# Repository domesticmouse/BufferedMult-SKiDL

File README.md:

# Eurorack Buffered Multiple (SKiDL + KiCad 10)

A precision **Triple 1-to-3 (Normalized to 1-to-6 / 1-to-9) Eurorack Buffered Multiple** designed in Python using [SKiDL](https://devbisme.github.io/skidl/) and targeting **KiCad 10**.

This project is a SKiDL re-implementation and 3-channel expansion of [domesticmouse/Buffered-Mult](https://github.com/domesticmouse/Buffered-Mult), omitting the LED feedback circuitry.

**Interactive Course & Tutorial:** [**https://domesticmouse.github.io/BufferedMult-SKiDL/**](https://domesticmouse.github.io/BufferedMult-SKiDL/) *(published via GitHub Pages from [`tutorial/`](tutorial/))*

---

## Features & Architecture

- **Triple 1-to-3 / Cascaded 1-to-6 / 1-to-9 Routing**:
  - **Channel 1**: 1 input (`IN_1`) driving 3 individually buffered outputs (`OUT_1A`, `OUT_1B`, `OUT_1C`). When `IN_1` is unpatched, its normalled switch contact (`TN`) grounds the input to `0V`.
  - **Channel 2**: 1 input (`IN_2`) driving 3 individually buffered outputs (`OUT_2A`, `OUT_2B`, `OUT_2C`). When `IN_2` is unpatched, its normalled switch contact (`TN`) receives the buffered signal from Channel 1 (`CH1_BUF`), cascading Channels 1 and 2 into a **1-to-6 buffered multiple** with zero loading droop between channels. Patching a cable into `IN_2` breaks the normal connection for independent channel operation.
  - **Channel 3**: 1 input (`IN_3`) driving 3 individually buffered outputs (`OUT_3A`, `OUT_3B`, `OUT_3C`). When `IN_3` is unpatched, its normalled switch contact (`TN`) receives the buffered signal from Channel 2 (`CH2_BUF`), cascading all three channels into a **1-to-9 buffered multiple** (or a **1-to-3 + 1-to-6** split if `IN_2` is patched while `IN_3` is unpatched). Patching a cable into `IN_3` breaks the normal connection for independent triple 1-to-3 operation.
- **Dedicated Input & Output Buffering**:
  - Each channel uses one quad `TL074H` (`TL074HIDR`) op-amp (`SOIC-14`):
    - **Stage A**: Unity-gain input follower protected by a `PESD12VL1BA` (`SOD-323`) bidirectional 12V TVS/ESD diode, a `100K` input pull-down resistor (`0603`), and a `1K` series input current-limiting resistor (`0603`).
    - **Stages B, C, D**: Three independent unity-gain output followers, each isolated with a `470R` series output protection resistor (`0603`).
- **Eurorack Power Supply Protection**:
  - Standard 10-pin (`2x5`) through-hole shrouded IDC power header (`±12V`, `GND`).
  - Reverse-polarity protection via `1N5819WS` Schottky diodes (`SOD-323`, or `B5819W` in `SOD-123` as a larger alternative).
  - `10uF` radial through-hole electrolytic bulk bypass capacitors per rail plus `100nF` (`0603`) local ceramic decoupling capacitors at each op-amp's `V+` and `V-` pins.

### Signal Flow

```mermaid
flowchart LR
    subgraph CH1["Channel 1 (U1: TL074H)"]
        J_IN1["IN_1 Jack<br/>(TN -> GND)"] --> TVS1["PESD12VL1BA TVS<br/>+ 100K to GND"]
        TVS1 --> R_IN1["1K Series"] --> U1A["U1A Input Buffer"]
        U1A --> U1B["U1B Buffer + 470R"] --> OUT_1A["OUT_1A Jack"]
        U1A --> U1C["U1C Buffer + 470R"] --> OUT_1B["OUT_1B Jack"]
        U1A --> U1D["U1D Buffer + 470R"] --> OUT_1C["OUT_1C Jack"]
    end

    subgraph CH2["Channel 2 (U2: TL074H)"]
        J_IN2["IN_2 Jack<br/>(TN <- CH1_BUF)"] --> TVS2["PESD12VL1BA TVS<br/>+ 100K to GND"]
        TVS2 --> R_IN2["1K Series"] --> U2A["U2A Input Buffer"]
        U2A --> U2B["U2B Buffer + 470R"] --> OUT_2A["OUT_2A Jack"]
        U2A --> U2C["U2C Buffer + 470R"] --> OUT_2B["OUT_2B Jack"]
        U2A --> U2D["U2D Buffer + 470R"] --> OUT_2C["OUT_2C Jack"]
    end

    subgraph CH3["Channel 3 (U3: TL074H)"]
        J_IN3["IN_3 Jack<br/>(TN <- CH2_BUF)"] --> TVS3["PESD12VL1BA TVS<br/>+ 100K to GND"]
        TVS3 --> R_IN3["1K Series"] --> U3A["U3A Input Buffer"]
        U3A --> U3B["U3B Buffer + 470R"] --> OUT_3A["OUT_3A Jack"]
        U3A --> U3C["U3C Buffer + 470R"] --> OUT_3B["OUT_3B Jack"]
        U3A --> U3D["U3D Buffer + 470R"] --> OUT_3C["OUT_3C Jack"]
    end

    U1A -- "CH1_BUF (Normalled to IN_2 TN)" --> J_IN2
    U2A -- "CH2_BUF (Normalled to IN_3 TN)" --> J_IN3
```

---

## Bill of Materials (BOM)

The design separates **SMT components** (factory-assembled on `B.Cu` by JLCPCB) from **Through-Hole (THT) components** (hand-soldered after receiving the boards):

| Ref | Qty | Value / Part | Package / Footprint | KiCad Symbol | LCSC Part # | Assembly / Description |
| :--- | --: | :--- | :--- | :--- | :--- | :--- |
| `U1`–`U3` | 3 | `TL074H` (`TL074HIDR`) | `Package_SO:SOIC-14_3.9x8.7mm_P1.27mm` | `Amplifier_Operational:TL074` | `C2878713` | **SMT (`B.Cu`, Extended)** — Quad Low-Noise High-Voltage Op-Amp |
| `D1`, `D2` | 2 | `1N5819WS` | `Diode_SMD:D_SOD-323` | `Device:D_Schottky` | `C191023` | **SMT (`B.Cu`, Basic)** — Schottky Reverse-Polarity Protection Diode *(Alt larger package: `B5819W` in `Diode_SMD:D_SOD-123`, LCSC `C8598`, Basic)* |
| `D3`–`D5` | 3 | `PESD12VL1BA` (`PESD12VL1BA,115`) | `Diode_SMD:D_SOD-323` | `Device:D_TVS` | `C38558` | **SMT (`B.Cu`, Extended)** — 12V Bidirectional Low-Capacitance (`19 pF`, `<50 nA`) Input ESD/TVS Protection Diode *(Alt 15V: `PESD15VL1BA,115` / `C85378`; Basic SOD-123FL: `SMF12CA` / `C19077508`)* |
| `C3`–`C8` | 6 | `100nF` (`50V X7R`) | `Capacitor_SMD:C_0603_1608Metric` | `Device:C` | `C14663` | **SMT (`B.Cu`, Basic)** — Ceramic Decoupling Capacitor (`CC0603KRX7R9BB104`) |
| `R1`, `R6`, `R11` | 3 | `100K` (`1%`) | `Resistor_SMD:R_0603_1608Metric` | `Device:R` | `C25803` | **SMT (`B.Cu`, Basic)** — Input Pull-Down Resistor (`0603WAF1003T5E`) |
| `R2`, `R7`, `R12` | 3 | `1K` (`1%`) | `Resistor_SMD:R_0603_1608Metric` | `Device:R` | `C21190` | **SMT (`B.Cu`, Basic)** — Input Series Overvoltage / ESD Current-Limiting Resistor (`0603WAF1001T5E`) |
| `R3`–`R5`, `R8`–`R10`, `R13`–`R15` | 9 | `470R` (`1%`) | `Resistor_SMD:R_0603_1608Metric` | `Device:R` | `C23179` | **SMT (`B.Cu`, Basic)** — Output Series Protection Resistor (`0603WAF4700T5E`) |
| `J2`–`J13` | 12 | `WQP-PJ398SM` | `Connector_Audio:Jack_3.5mm_QingPu_WQP-PJ398SM_Vertical_CircularHoles` | `Connector_Audio:AudioJack2_SwitchT` | — | **THT (`F.Cu`, Hand-Soldered)** — 3.5mm Mono Switched Eurorack Jack (Thonkiconn) |
| `C1`, `C2` | 2 | `10uF` (`25V`) | `Capacitor_THT:CP_Radial_D5.0mm_P2.00mm` | `Device:C_Polarized` | `C713347` | **THT (`F.Cu`, Hand-Soldered)** — Radial Electrolytic Bulk Cap (`ECEA1EKS100`) |
| `J1` | 1 | `EURORACK_PWR_10PIN` | `Connector_IDC:IDC-Header_2x05_P2.54mm_Vertical` | `Connector_Generic:Conn_02x05_Odd_Even` | — | **THT (`B.Cu`, Hand-Soldered)** — 10-Pin (`2x5`) Shrouded Eurorack Power Header |

---

## Getting Started

### Prerequisites

- **KiCad 10** installed (default macOS symbol/footprint path `/Applications/KiCad/KiCad.app/Contents/SharedSupport/` is detected automatically by `buffered_multiple.py`).
- **Python 3.12–3.14** and [`uv`](https://docs.astral.sh/uv/).

### Setup & Run

1. **Create the virtual environment and install dependencies**:
   ```bash
   uv venv --clear --python 3.14 .venv
   uv pip install skidl markdown-it-py pyyaml
   ```

2. **Generate the circuit outputs and run Electrical Rules Checking (ERC)**:
   ```bash
   .venv/bin/python buffered_multiple.py
   ```

3. **Generate or update the 4HP Eurorack front panel PCB and Gerbers**:
   ```bash
   /Applications/KiCad/KiCad.app/Contents/Frameworks/Python.framework/Versions/Current/bin/python3 \
       .agents/skills/eurorack-panel/scripts/generate_eurorack_panel.py \
       --main-pcb BufferedMult.kicad_pcb \
       --output BufferedMult_Panel.kicad_pcb \
       --title "BUF MULT" \
       --subtitle "1:3 / 1:6 / 1:9" \
       --gerber-dir production/panel \
       --zip production/BufferedMult_Panel.zip \
       --drc
   ```

4. **Build and validate the interactive tutorial HTML from Markdown** (optional, for local previewing; GitHub Actions automatically builds and publishes to [**GitHub Pages**](https://domesticmouse.github.io/BufferedMult-SKiDL/) via [`.github/workflows/pages.yml`](.github/workflows/pages.yml)):
   ```bash
   .venv/bin/python tutorial/build.py --check
   ```

5. **Lint and format with `ruff`**:
   ```bash
   ruff check --fix buffered_multiple.py buffered_multiple_sklib.py tutorial/build.py && ruff format buffered_multiple.py buffered_multiple_sklib.py tutorial/build.py
   ```

---

## Generated Files

Running `buffered_multiple.py` produces:

- **`buffered_multiple.net`** — KiCad 10 netlist with deterministic hierarchical `tstamps` and `Power` / `Signal` net classes.
- **`buffered_multiple_bom.xml`** — KiCad XML Bill of Materials.
- **`buffered_multiple_jlcpcb_bom.csv`** — Grouped JLCPCB SMT PCBA Bill of Materials (`Comment,Designator,Footprint,LCSC Part #`), excluding hand-soldered THT parts by default.
- **`buffered_multiple.erc`** / **`buffered_multiple.log`** — SKiDL ERC report and execution log (`0` errors, `0` warnings).
- **`buffered_multiple_sklib.py`** — Auto-generated SKiDL backup symbol library.

---

## KiCad 10 PCBs & Fabrication Outputs

Both the main circuit board and a mated 3U × 4HP Eurorack front panel are included in the repository:

- **Main Circuit PCB ([`BufferedMult.kicad_pro`](BufferedMult.kicad_pro) / [`BufferedMult.kicad_pcb`](BufferedMult.kicad_pcb))**:
  - **Dimensions**: `20.0 × 109.0 mm` (4HP, Rev `V2.0`), 2-layer PCB with stitched `F.Cu` and `B.Cu` `GND` planes and `0.5 mm` `±12V` power spines.
  - **Assembly**: Full 3-channel (44-component) layout with single-sided SMT placement on `B.Cu` (29 SMD parts) and hand-soldered THT jacks/bulk caps on `F.Cu` (`J2`–`J13`, `C1`, `C2`) plus the 10-pin power header on `B.Cu` (`J1`), complete with a `-12V` orientation knockout, `V2.0` revision marking, and repository URL on `B.SilkS`.
- **4HP Eurorack Front Panel ([`BufferedMult_Panel.kicad_pro`](BufferedMult_Panel.kicad_pro) / [`BufferedMult_Panel.kicad_pcb`](BufferedMult_Panel.kicad_pcb))**:
  - **Dimensions**: `20.0 × 128.5 mm` (Doepfer A-100 3U × 4HP standard).
  - **Features**: 12× `6.2 mm` PTH grounded jack cutouts aligned to the `+6.48 mm` `WQP-PJ398SM` (Thonkiconn) bushing centers (`14.40 mm` uniform vertical row pitch), 2× `3.2 × 5.5 mm` NPTH M3 mounting slots, exposed `F.Mask` copper/finish graphics (`BUF MULT` title, input callout badges for `IN 1` / `IN 2` / `IN 3`, and normalling cascade indicators), `F.SilkS` jack labels and `TL074` callout, and solid `F.Cu` / `B.Cu` copper shield planes with exposed rear ground rings.
- **Fabrication Archives (`production/`)**:
  - [`production/BufferedMult.zip`](production/BufferedMult.zip) — Main PCB Gerbers and Excellon drill files.
  - [`production/BufferedMult_Panel.zip`](production/BufferedMult_Panel.zip) — 4HP Front Panel Gerbers and Excellon drill files (also unpacked in `production/panel/`).
  - [`production/positions.csv`](production/positions.csv), [`production/bom.csv`](production/bom.csv), [`production/designators.csv`](production/designators.csv), [`production/netlist.ipc`](production/netlist.ipc) — Fabrication Toolkit pick-and-place, BOM, and IPC-D-356 netlist files (use [`buffered_multiple_jlcpcb_bom.csv`](buffered_multiple_jlcpcb_bom.csv) for SMT-only JLCPCB assembly).

---

## Interactive Course & Tutorial (`tutorial/`)

The repository includes an 8-lesson interactive **Hardware-as-Code** course published at [**https://domesticmouse.github.io/BufferedMult-SKiDL/**](https://domesticmouse.github.io/BufferedMult-SKiDL/) (authored in Markdown under [`tutorial/`](tutorial/) and compiled via [`tutorial/build.py`](tutorial/build.py)). Starting from an empty Python file, the lessons progressively grow [`buffered_multiple.py`](buffered_multiple.py) and its post-netlist PCB, front-panel, and pre-fab verification scripts:

| Lesson | Stage & Title | Markdown Source | Runnable Companion App |
| :--- | :--- | :--- | :--- |
| **`0001`** | **Stage 1**: From an Empty File to KiCad 10 Bootstrap & First `ERC()` (`0 → 72 lines`) | [`0001-environment-and-kicad-bootstrap.md`](tutorial/lessons/0001-environment-and-kicad-bootstrap.md) | [`bootstrap_check.py`](tutorial/apps/0001-environment-and-kicad-bootstrap/bootstrap_check.py) |
| **`0002`** | **Stage 2**: Programmatic Part Discovery & Adding `FP_*` / `LCSC_*` Constants | [`0002-programmatic-component-discovery.md`](tutorial/lessons/0002-programmatic-component-discovery.md) | [`discover_parts.py`](tutorial/apps/0002-programmatic-component-discovery/discover_parts.py) |
| **`0003`** | **Stage 3**: Growing the Script — Adding `eurorack_power(vcc, vee, gnd)` (`68 → 155 lines`) | [`0003-eurorack-power-subcircuit.md`](tutorial/lessons/0003-eurorack-power-subcircuit.md) | [`power_subcircuit.py`](tutorial/apps/0003-eurorack-power-subcircuit/power_subcircuit.py) |
| **`0004`** | **Stage 4**: Growing the Script — Adding `buffered_channel_1to3()` (`155 → 255 lines`) | [`0004-single-buffered-channel.md`](tutorial/lessons/0004-single-buffered-channel.md) | [`single_channel.py`](tutorial/apps/0004-single-buffered-channel/single_channel.py) |
| **`0005`** | **Stage 5**: Completing `buffered_multiple.py` — Cascaded Normalling (`1:3 → 1:6 → 1:9`), `NetClass` & JLCPCB BOM (`255 → 334 lines`) | [`0005-cascaded-normalling-and-bom-export.md`](tutorial/lessons/0005-cascaded-normalling-and-bom-export.md) | [`buffered_multiple.py`](tutorial/apps/0005-cascaded-normalling-and-bom-export/buffered_multiple.py) |
| **`0006`** | **Stage 6**: From `.net` Netlist to 4HP KiCad 10 PCB Layout & Single-Sided SMT Assembly | [`0006-kicad-pcb-layout-and-assembly.md`](tutorial/lessons/0006-kicad-pcb-layout-and-assembly.md) | [`inspect_netlist_and_layout.py`](tutorial/apps/0006-kicad-pcb-layout-and-assembly/inspect_netlist_and_layout.py) |
| **`0007`** | **Stage 7**: Automated 4HP Eurorack Front Panel Generation in Python (`+6.48 mm` Bushing Offset) | [`0007-eurorack-front-panel-generator.md`](tutorial/lessons/0007-eurorack-front-panel-generator.md) | [`generate_panel_plan.py`](tutorial/apps/0007-eurorack-front-panel-generator/generate_panel_plan.py) |
| **`0008`** | **Stage 8 (Capstone)**: Programmatic Pre-Fab Design Review — Netlist-to-PCB Audit, DRC & Gerber Verification (`5/5 checks`) | [`0008-prefab-design-review-and-drc.md`](tutorial/lessons/0008-prefab-design-review-and-drc.md) | [`prefab_design_audit.py`](tutorial/apps/0008-prefab-design-review-and-drc/prefab_design_audit.py) |

### Printable Reference Sheets (`tutorial/reference/`)

- **[`skidl-cheatsheet.md`](tutorial/reference/skidl-cheatsheet.md)** — SKiDL API, pre-import KiCad 10 configuration, `dest=TEMPLATE`, `part.fields`, `u.p[n]` vs `u["V+"]`, `@subcircuit`, `NetClass`, and `ERC()` syntax cheat sheet.
- **[`kicad-jlcpcb-lookup.md`](tutorial/reference/kicad-jlcpcb-lookup.md)** — Four-step programmatic component discovery workflow (`search`, `show`, `search_footprints`, `jlcpcb_search.py`) and verified BOM pinout/LCSC table.
- **[`eurorack-power-and-normalling.md`](tutorial/reference/eurorack-power-and-normalling.md)** — Doepfer A-100 10-pin power header pinout, Schottky & bulk capacitor polarity, `WQP-PJ398SM` switched jack mechanics, and the `1:3 / 1:6 / 1:9` normalling truth table.
- **[`GLOSSARY.md`](tutorial/reference/GLOSSARY.md)** — Standardized SKiDL, KiCad 10, JLCPCB PCBA, and Eurorack hardware terminology.

---

## Documentation & Guides

- **[Interactive Tutorial on GitHub Pages (`domesticmouse.github.io/BufferedMult-SKiDL`)](https://domesticmouse.github.io/BufferedMult-SKiDL/)** — Hosted HTML edition of the 8-lesson (`0001`–`0008`) course and 4 reference sheets, built automatically by [`.github/workflows/pages.yml`](.github/workflows/pages.yml).
- **[`PCB_LAYOUT_GUIDE.md`](PCB_LAYOUT_GUIDE.md)** — Step-by-step KiCad 10 PCB layout, component placement, routing, and JLCPCB export guide.
- **[`FRONT_PANEL_GUIDE.md`](FRONT_PANEL_GUIDE.md)** — 4HP Eurorack front panel mechanical dimensions, bushing offset coordinate table, and automated generation workflow.
- **[`DESIGN_REVIEW.md`](DESIGN_REVIEW.md)** — Full schematic, PCB, DRC, Gerber, and EMC pre-compliance design review report.

---

## License

Licensed under the Apache License, Version 2.0. See [LICENSE.txt](LICENSE.txt) for details.

*This is not an official Google product.*

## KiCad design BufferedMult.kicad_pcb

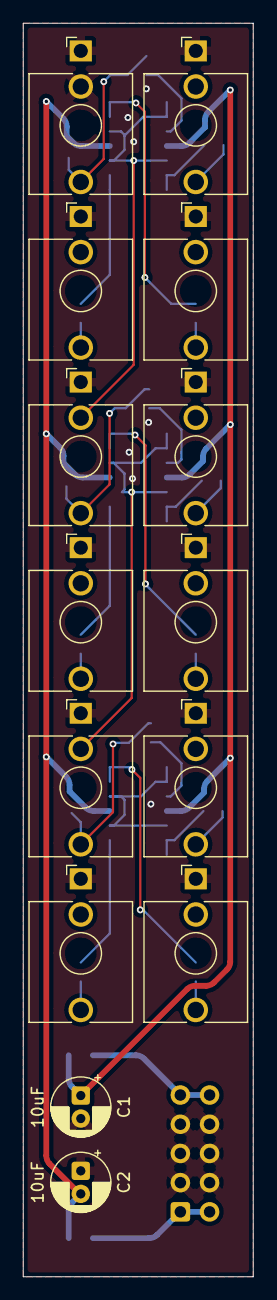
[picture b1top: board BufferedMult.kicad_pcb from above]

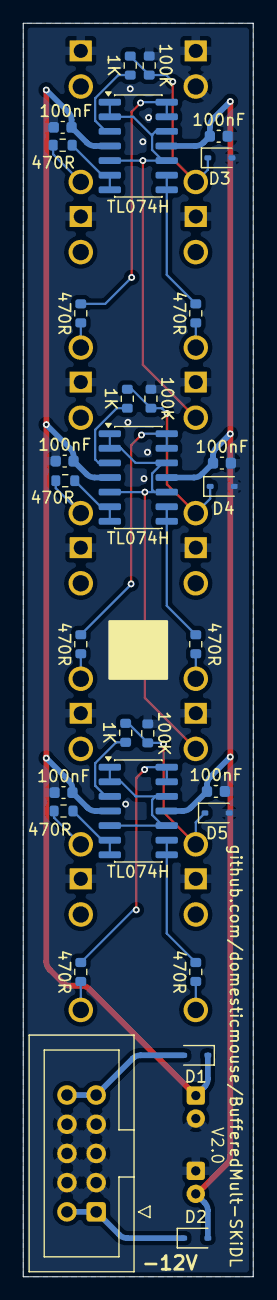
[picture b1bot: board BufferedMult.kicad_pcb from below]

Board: 2 copper layers, 20.0 x 109.0 mm, 44 parts (30 on the bottom side), 32 nets.

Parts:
C1, C2: 10uF; CP_Radial_D5.0mm_P2.00mm
C3, C4, C5, C6, C7, C8: 100nF; C_0603_1608Metric
D1, D2: 1N5819WS; D_SOD-323
D3, D4, D5: PESD12VL1BA; D_SOD-323
J1: EURORACK_PWR_10PIN; IDC-Header_2x05_P2.54mm_Vertical
J2: IN_1; Jack_3.5mm_QingPu_WQP-PJ398SM_Vertical_CircularHoles
J3: OUT_1A; Jack_3.5mm_QingPu_WQP-PJ398SM_Vertical_CircularHoles
J4: OUT_1B; Jack_3.5mm_QingPu_WQP-PJ398SM_Vertical_CircularHoles
J5: OUT_1C; Jack_3.5mm_QingPu_WQP-PJ398SM_Vertical_CircularHoles
J6: IN_2; Jack_3.5mm_QingPu_WQP-PJ398SM_Vertical_CircularHoles
J7: OUT_2A; Jack_3.5mm_QingPu_WQP-PJ398SM_Vertical_CircularHoles
J8: OUT_2B; Jack_3.5mm_QingPu_WQP-PJ398SM_Vertical_CircularHoles
J9: OUT_2C; Jack_3.5mm_QingPu_WQP-PJ398SM_Vertical_CircularHoles
J10: IN_3; Jack_3.5mm_QingPu_WQP-PJ398SM_Vertical_CircularHoles
J11: OUT_3A; Jack_3.5mm_QingPu_WQP-PJ398SM_Vertical_CircularHoles
J12: OUT_3B; Jack_3.5mm_QingPu_WQP-PJ398SM_Vertical_CircularHoles
J13: OUT_3C; Jack_3.5mm_QingPu_WQP-PJ398SM_Vertical_CircularHoles
R1, R6, R11: 100K; R_0603_1608Metric
R2, R7, R12: 1K; R_0603_1608Metric
R3, R4, R5, R8, R9, R10, R13, R14, R15: 470R; R_0603_1608Metric
U1, U2, U3: TL074H; SOIC-14_3.9x8.7mm_P1.27mm

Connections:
+12V: C1.1, C3.1, C5.1, C7.1, D1.1, U1.4, U2.4, U3.4
+12V_RAW: D1.2, J1.9, J1.10
-12V: C2.2, C4.2, C6.2, C8.2, D2.2, U1.11, U2.11, U3.11
-12V_RAW: D2.1, J1.1, J1.2
CH1_BUF: J6.TN, U1.1, U1.2, U1.5, U1.10, U1.12
CH1_IN: R2.2, U1.3
CH1_JACK_IN: D3.1, J2.T, R1.1, R2.1
CH1_OP_A: R3.1, U1.6, U1.7
CH1_OP_B: R4.1, U1.8, U1.9
CH1_OP_C: R5.1, U1.13, U1.14
CH1_OUT_A: J3.T, R3.2
CH1_OUT_B: J4.T, R4.2
CH1_OUT_C: J5.T, R5.2
CH2_BUF: J10.TN, U2.1, U2.2, U2.5, U2.10, U2.12
CH2_IN: R7.2, U2.3
CH2_JACK_IN: D4.1, J6.T, R6.1, R7.1
CH2_OP_A: R8.1, U2.6, U2.7
CH2_OP_B: R9.1, U2.8, U2.9
CH2_OP_C: R10.1, U2.13, U2.14
CH2_OUT_A: J7.T, R8.2
CH2_OUT_B: J8.T, R9.2
CH2_OUT_C: J9.T, R10.2
CH3_BUF: U3.1, U3.2, U3.5, U3.10, U3.12
CH3_IN: R12.2, U3.3
CH3_JACK_IN: D5.1, J10.T, R11.1, R12.1
CH3_OP_A: R13.1, U3.6, U3.7
CH3_OP_B: R14.1, U3.8, U3.9
CH3_OP_C: R15.1, U3.13, U3.14
CH3_OUT_A: J11.T, R13.2
CH3_OUT_B: J12.T, R14.2
CH3_OUT_C: J13.T, R15.2
GND: C1.2, C2.1, C3.2, C4.1, C5.2, C6.1, C7.2, C8.1, D3.2, D4.2, D5.2, J1.3, J1.4, J1.5, J1.6, J1.7, J1.8, J2.S, J2.TN, J3.S, J4.S, J5.S, J6.S, J7.S, J8.S, J9.S, J10.S, J11.S, J12.S, J13.S, R1.2, R6.2, R11.2

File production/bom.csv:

Designator,Footprint,Quantity,Value,LCSC Part #
"C1, C2",CP_Radial_D5.0mm_P2.00mm,2,10uF,ECEA1EKS100
"C3, C4, C5, C6, C7, C8",0603,6,100nF,C14663
"D1, D2",D_SOD-323,2,1N5819WS,C191023
"D3, D4, D5",D_SOD-323,3,PESD12VL1BA,C38558
J1,IDC-Header_2x05_P2.54mm_Vertical,1,EURORACK_PWR_10PIN,
J10,Jack_3.5mm_QingPu_WQP-PJ398SM_Vertical_CircularHoles,1,IN_3,WQP-PJ398SM
J11,Jack_3.5mm_QingPu_WQP-PJ398SM_Vertical_CircularHoles,1,OUT_3A,WQP-PJ398SM
J12,Jack_3.5mm_QingPu_WQP-PJ398SM_Vertical_CircularHoles,1,OUT_3B,WQP-PJ398SM
J13,Jack_3.5mm_QingPu_WQP-PJ398SM_Vertical_CircularHoles,1,OUT_3C,WQP-PJ398SM
J2,Jack_3.5mm_QingPu_WQP-PJ398SM_Vertical_CircularHoles,1,IN_1,WQP-PJ398SM
J3,Jack_3.5mm_QingPu_WQP-PJ398SM_Vertical_CircularHoles,1,OUT_1A,WQP-PJ398SM
J4,Jack_3.5mm_QingPu_WQP-PJ398SM_Vertical_CircularHoles,1,OUT_1B,WQP-PJ398SM
J5,Jack_3.5mm_QingPu_WQP-PJ398SM_Vertical_CircularHoles,1,OUT_1C,WQP-PJ398SM
J6,Jack_3.5mm_QingPu_WQP-PJ398SM_Vertical_CircularHoles,1,IN_2,WQP-PJ398SM
J7,Jack_3.5mm_QingPu_WQP-PJ398SM_Vertical_CircularHoles,1,OUT_2A,WQP-PJ398SM
J8,Jack_3.5mm_QingPu_WQP-PJ398SM_Vertical_CircularHoles,1,OUT_2B,WQP-PJ398SM
J9,Jack_3.5mm_QingPu_WQP-PJ398SM_Vertical_CircularHoles,1,OUT_2C,WQP-PJ398SM
"R1, R11, R6",0603,3,100K,C25803
"R10, R13, R14, R15, R3, R4, R5, R8, R9",0603,9,470R,C23179
"R12, R2, R7",0603,3,1K,C21190
"U1, U2, U3",SOIC-14_3.9x8.7mm_P1.27mm,3,TL074H,C2878713
